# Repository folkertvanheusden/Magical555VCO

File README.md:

Magical555VCO
-------------

This is a very simple 555 timer based dual VCO.
It fits nicely in any eurorack.

Sample output: https://vanheusden.com/permshare/magical555vco-v0.2.flac
or listen in your browser at: https://vanheusden.com/electronics/Magical555VCO/audio-player.php

* schematics are under media/magical555vco.pdf

Folkert van Heusden <mail@vanheusden.com>

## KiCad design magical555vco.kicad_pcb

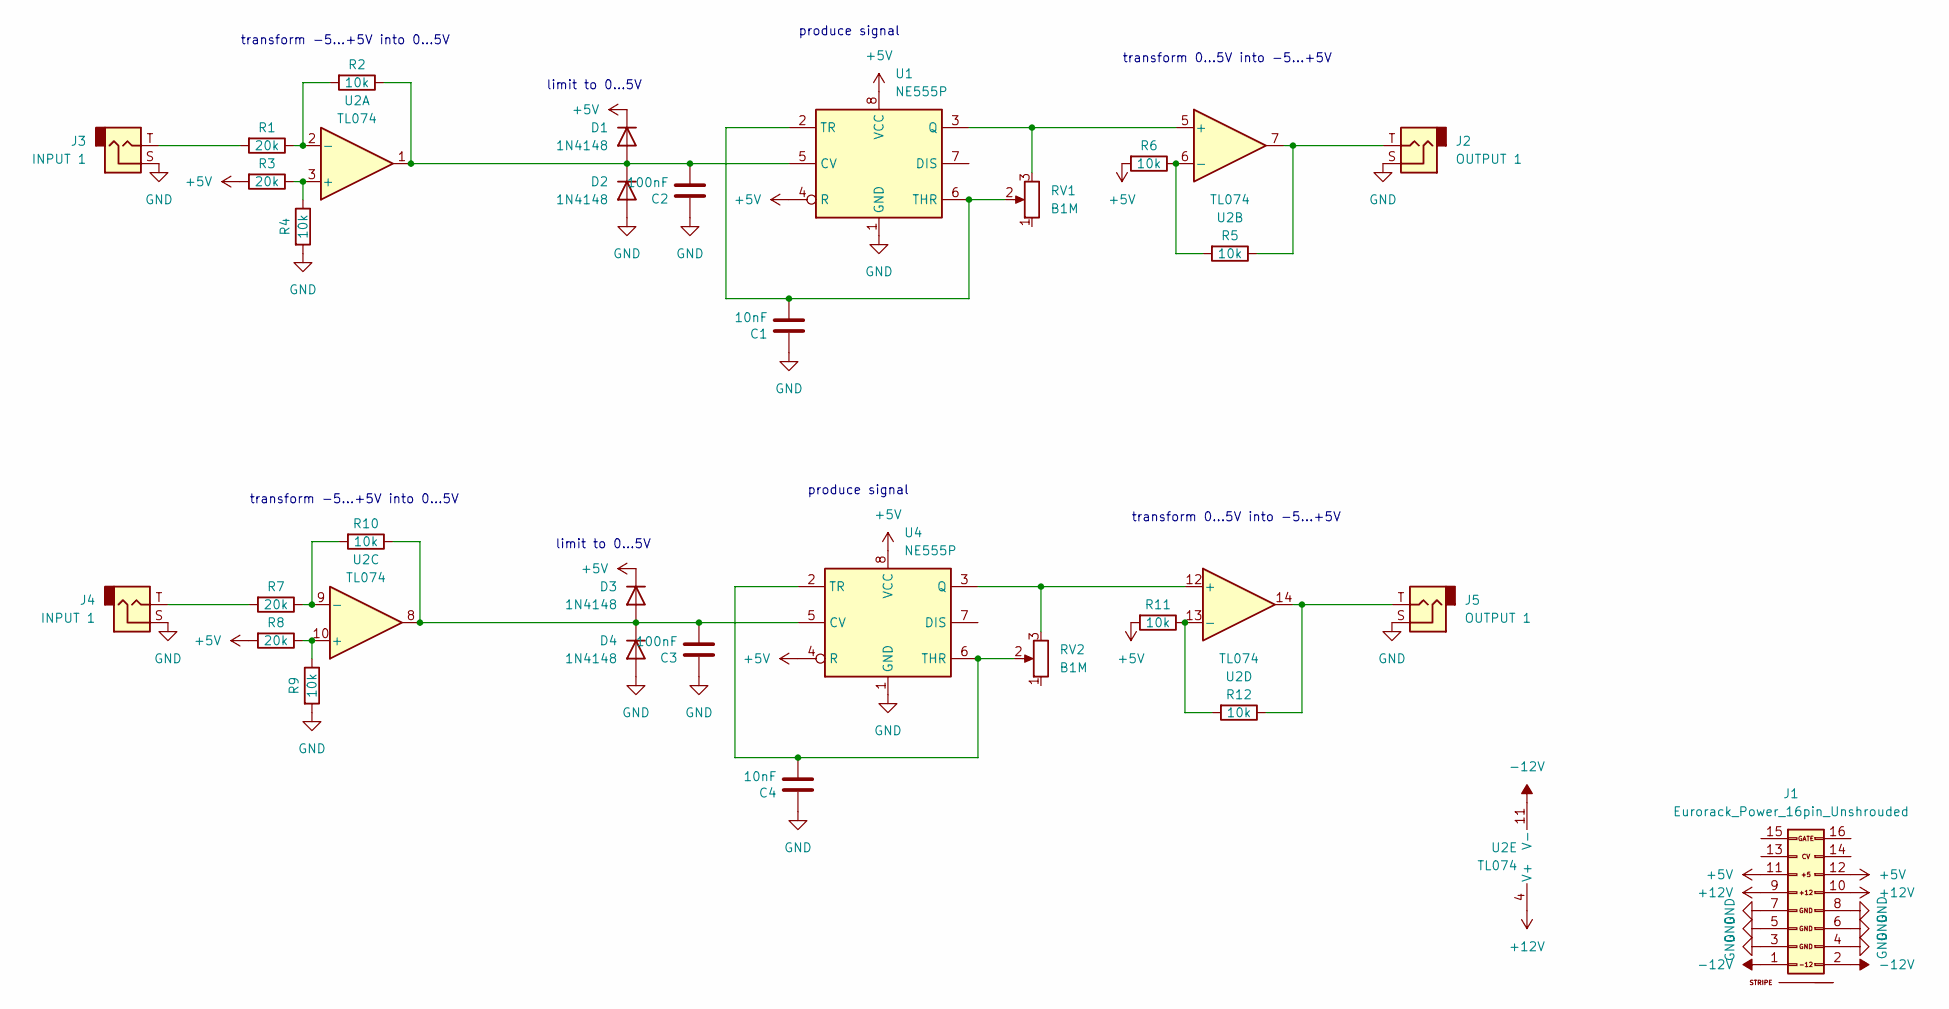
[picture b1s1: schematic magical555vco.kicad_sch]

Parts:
C1, C4: 10nF; C_Disc_D5.0mm_W2.5mm_P5.00mm
C2, C3: 100nF; C_Disc_D5.0mm_W2.5mm_P5.00mm
D1, D2, D3, D4: 1N4148; D_DO-35_SOD27_P7.62mm_Horizontal
J1: Eurorack_Power_16pin_Unshrouded; Pins_2x08_2.54mm_TH_EurorackPower; Part Number 1-1602FBV0T
J2, J5: OUTPUT 1; Jack_3.5mm_QingPu_WQP-PJ398SM_Vertical_CircularHoles
J3, J4: INPUT 1; Jack_3.5mm_QingPu_WQP-PJ398SM_Vertical_CircularHoles
R1, R3, R7, R8: 20k; R_Axial_DIN0204_L3.6mm_D1.6mm_P7.62mm_Horizontal
R2, R4, R5, R6, R9, R10, R11, R12: 10k; R_Axial_DIN0204_L3.6mm_D1.6mm_P7.62mm_Horizontal
RV1, RV2: B1M; Potentiometer_Alps_RK09K_Single_Vertical
U1, U4: NE555P; DIP-8_W7.62mm
U2: TL074; DIP-14_W7.62mm_Socket_LongPads

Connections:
+5V: D1.1 (K), D3.1 (K), J1.11 (5V), J1.12 (5V), R3.2, R6.2, R8.2, R11.2, U1.4 (R), U1.8 (VCC), U4.4 (R), U4.8 (VCC)
+12V: J1.9 (+12V), J1.10 (+12V), U2.4 (V+)
-12V: J1.1 (-12V), J1.2 (-12V), U2.11 (V-)
GND: C1.1, C2.1, C3.1, C4.1, D2.2 (A), D4.2 (A), J1.3 (GND), J1.4 (GND), J1.5 (GND), J1.6 (GND), J1.7 (GND), J1.8 (GND), J2.S, J3.S, J4.S, J5.S, R4.2, R9.2, U1.1 (GND), U4.1 (GND)
unnamed: C2.2, D1.2 (A), D2.1 (K), R2.1, U1.5 (CV), U2.1
unnamed: C3.2, D3.2 (A), D4.1 (K), R10.1, U2.8, U4.5 (CV)
unnamed: J2.T, R5.1, U2.7
unnamed: J3.T, R1.2
unnamed: J4.T, R7.2
unnamed: J5.T, R12.1, U2.14
unnamed: RV1.3, U1.3 (Q), U2.5 (+)
unnamed: C1.2, RV1.2, U1.2 (TR), U1.6 (THR)
unnamed: R3.1, R4.1, U2.3 (+)
unnamed: R1.1, R2.2, U2.2 (-)
unnamed: R5.2, R6.1, U2.6 (-)
unnamed: R8.1, R9.1, U2.10 (+)
unnamed: R7.1, R10.2, U2.9 (-)
unnamed: RV2.3, U2.12 (+), U4.3 (Q)
unnamed: R11.1, R12.2, U2.13 (-)
unnamed: C4.2, RV2.2, U4.2 (TR), U4.6 (THR)

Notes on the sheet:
limit to 0...5V
transform 0...5V into -5...+5V
produce signal
transform -5...+5V into 0...5V

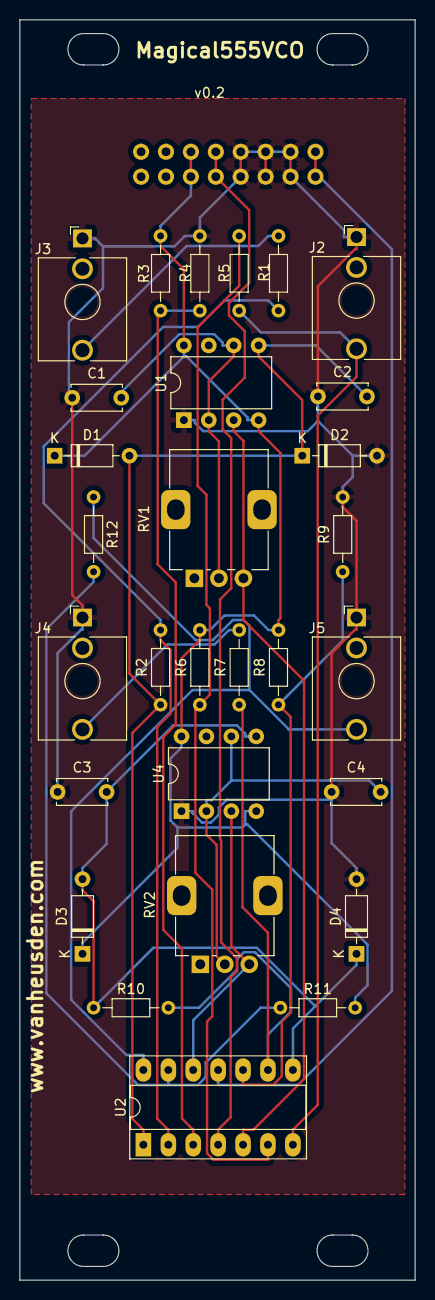
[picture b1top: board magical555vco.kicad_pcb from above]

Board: 2 copper layers, 40.3 x 128.5 mm, 30 parts (1 on the bottom side), 20 nets.

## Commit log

2023-10-14 basic version, 1 channel
2023-10-14 2 modules, potmeter
2023-10-21 v0.2
2023-10-28 meta
2023-10-28 media
2023-10-28 audio link
